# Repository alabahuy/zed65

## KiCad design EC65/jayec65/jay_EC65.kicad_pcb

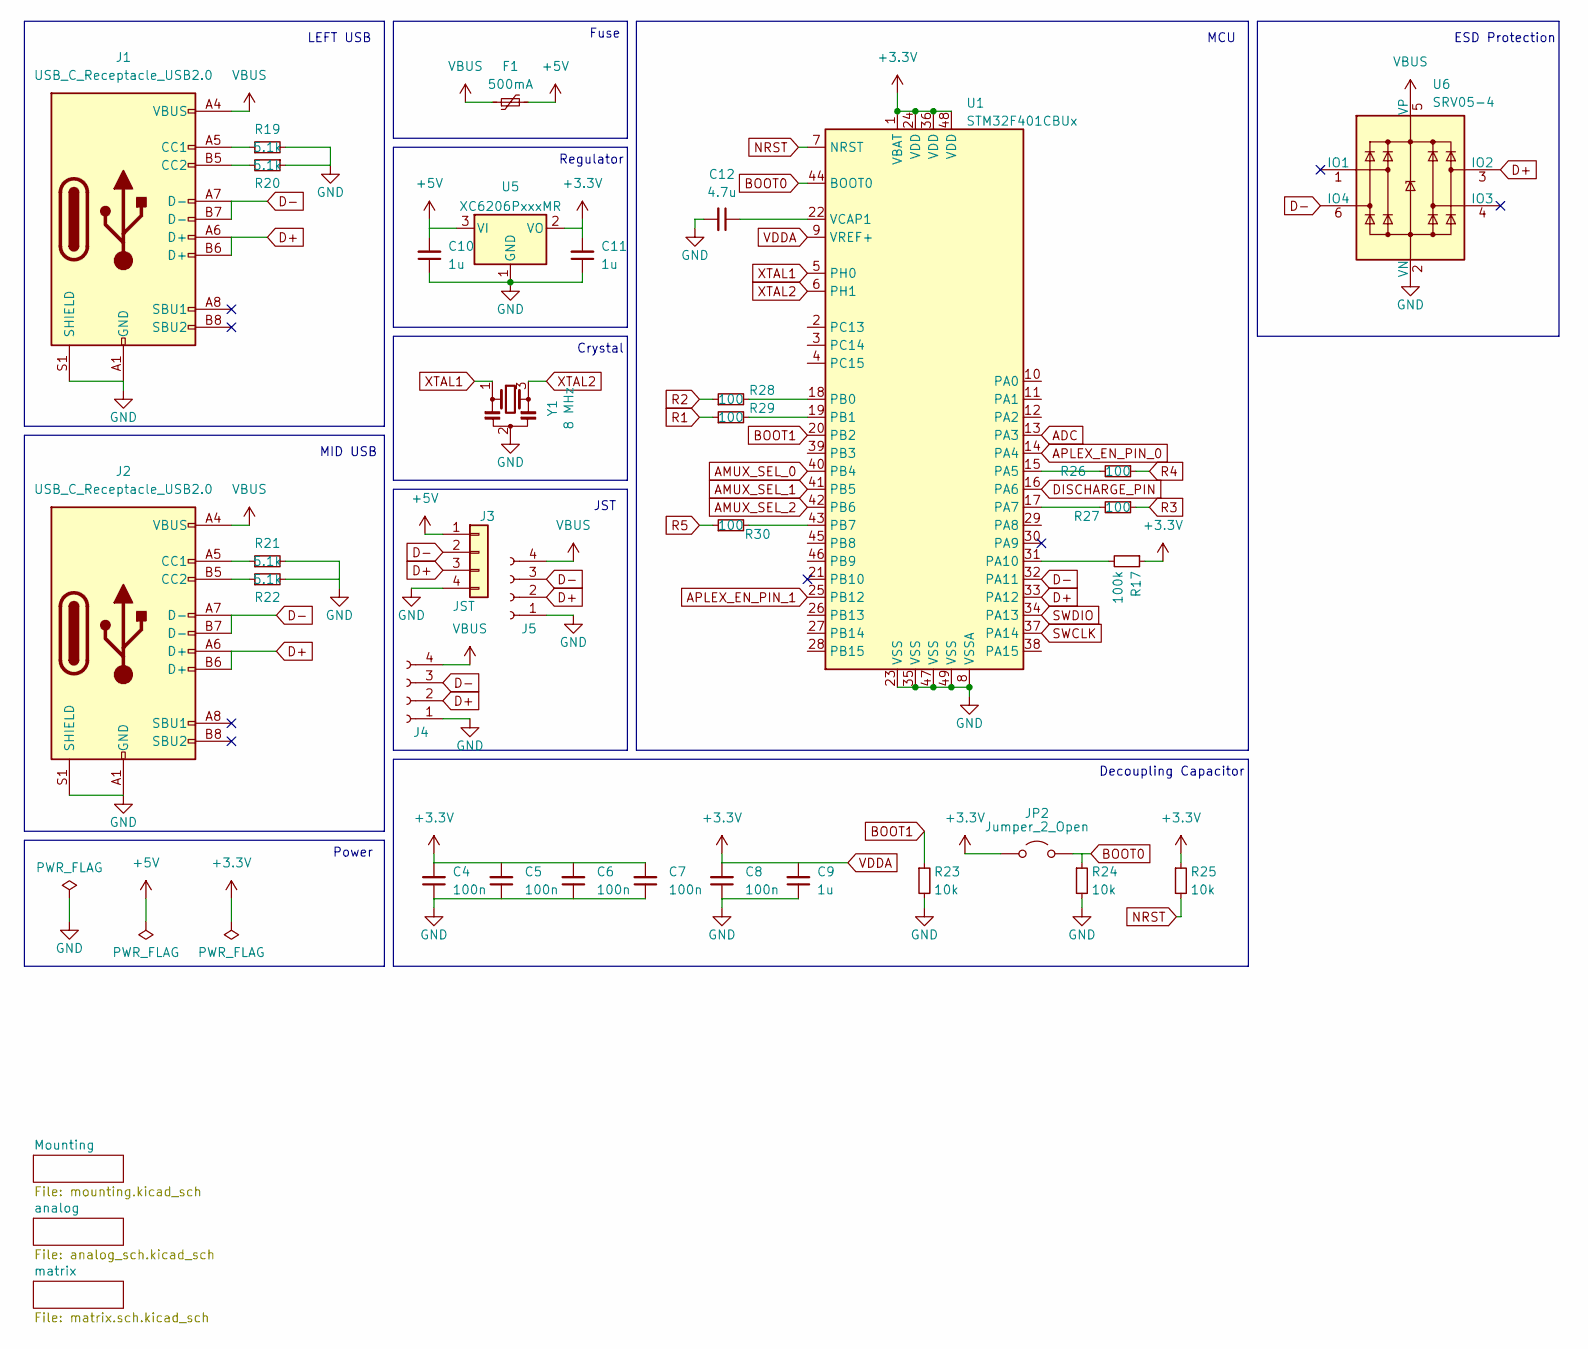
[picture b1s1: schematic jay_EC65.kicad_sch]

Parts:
C4, C5, C6, C7, C8: 100n; C_0603_1608Metric; LCSC C14663
C9, C10, C11: 1u; C_0603_1608Metric; LCSC C15849
C12: 4.7u; C_0603_1608Metric; LCSC C19666
F1: 500mA; Fuse_1206_3216Metric
J1, J2: USB_C_Receptacle_USB2.0; USB_C_Receptacle_HRO_TYPE-C-31-M-12
J3: JST; JST-SR-4; LCSC C145956
J4, J5: Conn_01x04_Socket; PinHeader_1x04_P2.00mm_Vertical
JP2: Jumper_2_Open; PinHeader_1x02_P2.54mm_Vertical
R17: 100k; R_0603_1608Metric; LCSC C25803
R19, R20, R21, R22: 5.1k; R_0603_1608Metric; LCSC C23186
R23, R24, R25: 10k; R_0603_1608Metric; LCSC C25804
R26, R27, R28, R29, R30: 100; R_0603_1608Metric; LCSC C22775
U1: STM32F401CBUx; QFN-48-1EP_7x7mm_P0.5mm_EP5.6x5.6mm; MPN C118825; LCSC C118825
U5: XC6206PxxxMR; SOT-23; LCSC C5446
U6: SRV05-4; SOT-23-6_Handsoldering; LCSC C7420376
Y1: 8 MHz; Resonator_SMD_Murata_CSTxExxV-3Pin_3.0x1.1mm; LCSC C907975

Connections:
+5V: C10.2, F1.2, J3.1
ADC: U1.13 (PA3); also elsewhere on the board
AMUX_SEL_0: U1.40 (PB4); also elsewhere on the board
AMUX_SEL_1: U1.41 (PB5); also elsewhere on the board
AMUX_SEL_2: U1.42 (PB6); also elsewhere on the board
APLEX_EN_PIN_0: U1.14 (PA4); also elsewhere on the board
APLEX_EN_PIN_1: U1.25 (PB12); also elsewhere on the board
APLEX_OUT_PIN_0: U1.16 (PA6); also elsewhere on the board
BOOT0: JP2.2 (B), U1.44 (BOOT0)
BOOT1: R23.1, U1.20 (PB2)
D+: J1.A6 (D+), J1.B6 (D+), J2.A6 (D+), J2.B6 (D+), J3.3, J4.2, J5.2, U1.33 (PA12), U6.3 (IO2)
D-: J1.A7 (D-), J1.B7 (D-), J2.A7 (D-), J2.B7 (D-), J3.2, J4.3, J5.3, U1.32 (PA11), U6.6 (IO4)
GND: C4.1, C7.1, C8.1, C9.1, C10.1, C11.1, C12.2, J1.A1 (GND), J1.A12 (GND), J1.B1 (GND), J1.B12 (GND), J1.S1 (SHIELD), J2.A1 (GND), J2.A12 (GND), J2.B1 (GND), J2.B12 (GND), J2.S1 (SHIELD), J3.4, J4.1, J5.1, R19.2, R20.1, R21.2, R23.2, R24.2, U1.8 (VSSA), U1.23 (VSS), U1.35 (VSS), U1.47 (VSS), U1.49 (VSS), U5.1 (GND), U6.2 (VN), Y1.2; also elsewhere on the board
NRST: R25.2, U1.7 (NRST)
unnamed: J1.A5 (CC1), R19.1
unnamed: J1.B5 (CC2), R20.2
unnamed: J2.A5 (CC1), R21.1
unnamed: J2.B5 (CC2), R22.1
unnamed: R26.2, U1.15 (PA5)
unnamed: R27.2, U1.17 (PA7)
unnamed: R17.2, U1.31 (PA10)
unnamed: R28.2, U1.18 (PB0)
unnamed: R29.2, U1.19 (PB1)
unnamed: R30.2, U1.43 (PB7)
unnamed: C12.1, U1.22 (VCAP1)
R1: R29.1; also elsewhere on the board
R2: R28.1; also elsewhere on the board
R3: R27.1; also elsewhere on the board
R4: R26.1; also elsewhere on the board
R5: R30.1; also elsewhere on the board
SWCLK: U1.37 (PA14)
SWDIO: U1.34 (PA13)
VBUS: F1.1, J1.A4 (VBUS), J1.A9 (VBUS), J1.B4 (VBUS), J1.B9 (VBUS), J2.A4 (VBUS), J2.A9 (VBUS), J2.B4 (VBUS), J2.B9 (VBUS), J4.4, J5.4, U6.5 (VP)
VDDA: C4.2, C7.2, C8.2, C11.2, JP2.1 (A), R17.1, R25.1, U1.1 (VBAT), U1.9 (VREF+), U1.24 (VDD), U1.36 (VDD), U1.48 (VDD); also elsewhere on the board
XTAL1: U1.5 (PH0), Y1.1
XTAL2: U1.6 (PH1), Y1.3

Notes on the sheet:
Crystal
LEFT USB
Decoupling Capacitor
JST
MID USB
MCU
ESD Protection
Power
Fuse
Regulator

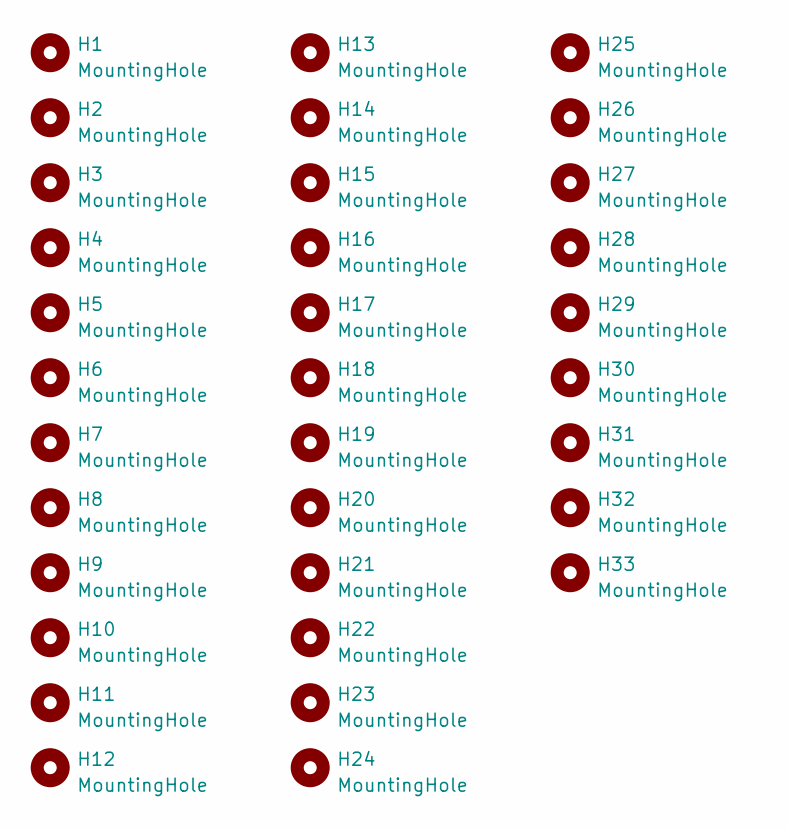
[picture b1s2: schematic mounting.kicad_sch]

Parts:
H1, H2, H3, H4, H5, H6, H7, H8, H9, H10, H11, H12, H13, H14, H15, H16, H17, H18, H19, H20, H21, H22, H23, H24, H25, H26, H27, H28, H29, H30, H31, H32, H33: MountingHole; HOLE_M2

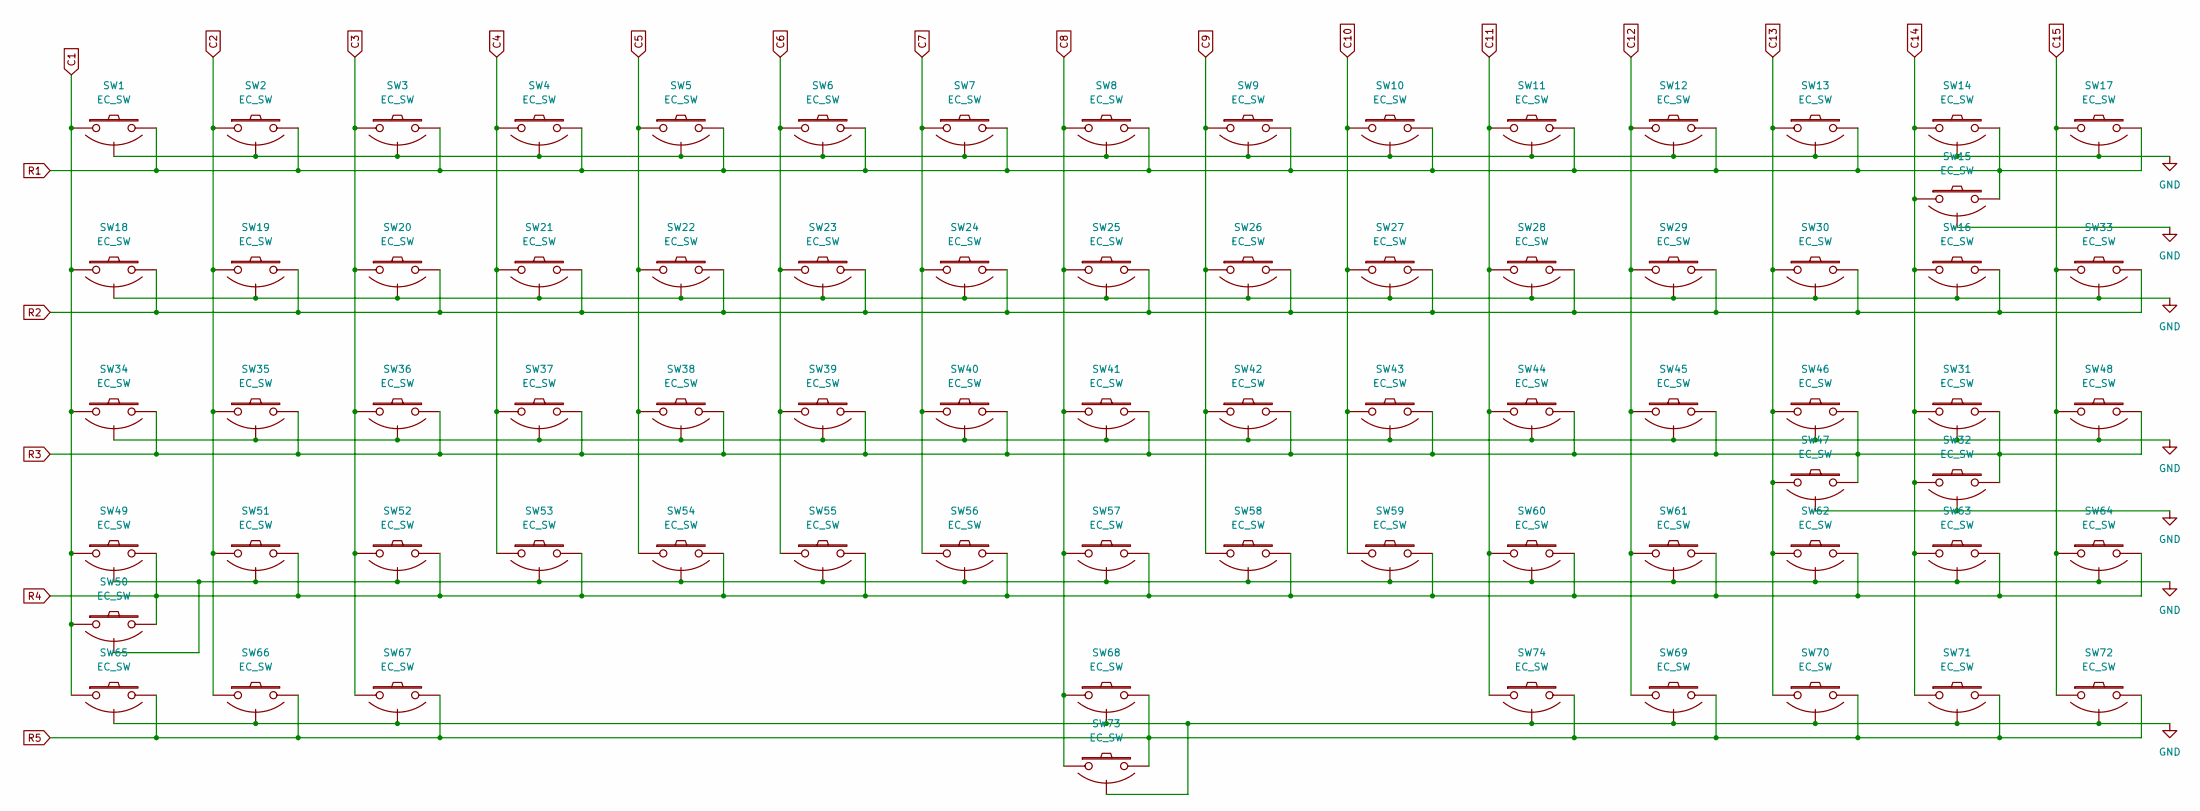
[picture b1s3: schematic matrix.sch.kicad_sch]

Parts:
SW1: EC_SW; ecs_pad_1U_no_ring_ 東プレ _十六条旭日旗
SW2, SW3, SW4, SW5, SW6, SW7, SW8, SW9, SW10, SW11, SW12, SW13, SW14, SW16, SW17, SW18, SW19, SW20, SW21, SW22, SW23, SW24, SW25, SW26, SW27, SW28, SW29, SW30, SW31, SW33, SW35, SW36, SW37, SW38, SW39, SW40, SW41, SW42, SW43, SW44, SW45, SW46, SW48, SW49, SW51, SW52, SW53, SW54, SW55, SW56, SW57, SW58, SW59, SW60, SW61, SW62, SW63, SW64, SW68, SW70, SW71, SW72, SW73, SW74: EC_SW; ecs_pad_1U_no_ring
SW15, SW32, SW47, SW50: EC_SW; ecs_pad_2U_no_ring
SW34: EC_SW; ecs_pad_0.25U_spaced_no_ring
SW65, SW66, SW67, SW69: EC_SW; ecs_pad_0.125U_spaced_no_ring

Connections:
C1: SW1.1, SW18.1, SW34.1, SW49.1, SW50.1, SW65.1; also elsewhere on the board
C2: SW2.1, SW19.1, SW35.1, SW51.1, SW66.1; also elsewhere on the board
C3: SW3.1, SW20.1, SW36.1, SW52.1, SW67.1; also elsewhere on the board
C4: SW4.1, SW21.1, SW37.1, SW53.1; also elsewhere on the board
C5: SW5.1, SW22.1, SW38.1, SW54.1; also elsewhere on the board
C6: SW6.1, SW23.1, SW39.1, SW55.1; also elsewhere on the board
C7: SW7.1, SW24.1, SW40.1, SW56.1; also elsewhere on the board
C8: SW8.1, SW25.1, SW41.1, SW57.1, SW68.1, SW73.1; also elsewhere on the board
C9: SW9.1, SW26.1, SW42.1, SW58.1; also elsewhere on the board
C10: SW10.1, SW27.1, SW43.1, SW59.1; also elsewhere on the board
C11: SW11.1, SW28.1, SW44.1, SW60.1, SW74.1; also elsewhere on the board
C12: SW12.1, SW29.1, SW45.1, SW61.1, SW69.1; also elsewhere on the board
C13: SW13.1, SW30.1, SW46.1, SW47.1, SW62.1, SW70.1; also elsewhere on the board
C14: SW14.1, SW15.1, SW16.1, SW31.1, SW32.1, SW63.1, SW71.1; also elsewhere on the board
C15: SW17.1, SW33.1, SW48.1, SW64.1, SW72.1; also elsewhere on the board
GND: SW1.3 (SG), SW2.3 (SG), SW3.3 (SG), SW4.3 (SG), SW5.3 (SG), SW6.3 (SG), SW7.3 (SG), SW8.3 (SG), SW9.3 (SG), SW10.3 (SG), SW11.3 (SG), SW12.3 (SG), SW13.3 (SG), SW14.3 (SG), SW15.3 (SG), SW16.3 (SG), SW17.3 (SG), SW18.3 (SG), SW19.3 (SG), SW20.3 (SG), SW21.3 (SG), SW22.3 (SG), SW23.3 (SG), SW24.3 (SG), SW25.3 (SG), SW26.3 (SG), SW27.3 (SG), SW28.3 (SG), SW29.3 (SG), SW30.3 (SG), SW31.3 (SG), SW32.3 (SG), SW33.3 (SG), SW34.3 (SG), SW35.3 (SG), SW36.3 (SG), SW37.3 (SG), SW38.3 (SG), SW39.3 (SG), SW40.3 (SG), SW41.3 (SG), SW42.3 (SG), SW43.3 (SG), SW44.3 (SG), SW45.3 (SG), SW46.3 (SG), SW47.3 (SG), SW48.3 (SG), SW49.3 (SG), SW50.3 (SG), SW51.3 (SG), SW52.3 (SG), SW53.3 (SG), SW54.3 (SG), SW55.3 (SG), SW56.3 (SG), SW57.3 (SG), SW58.3 (SG), SW59.3 (SG), SW60.3 (SG), SW61.3 (SG), SW62.3 (SG), SW63.3 (SG), SW64.3 (SG), SW65.3 (SG), SW66.3 (SG), SW67.3 (SG), SW68.3 (SG), SW69.3 (SG), SW70.3 (SG), SW71.3 (SG), SW72.3 (SG), SW73.3 (SG), SW74.3 (SG); also elsewhere on the board
R1: SW1.2, SW2.2, SW3.2, SW4.2, SW5.2, SW6.2, SW7.2, SW8.2, SW9.2, SW10.2, SW11.2, SW12.2, SW13.2, SW14.2, SW15.2, SW17.2; also elsewhere on the board
R2: SW16.2, SW18.2, SW19.2, SW20.2, SW21.2, SW22.2, SW23.2, SW24.2, SW25.2, SW26.2, SW27.2, SW28.2, SW29.2, SW30.2, SW33.2; also elsewhere on the board
R3: SW31.2, SW32.2, SW34.2, SW35.2, SW36.2, SW37.2, SW38.2, SW39.2, SW40.2, SW41.2, SW42.2, SW43.2, SW44.2, SW45.2, SW46.2, SW47.2, SW48.2; also elsewhere on the board
R4: SW49.2, SW50.2, SW51.2, SW52.2, SW53.2, SW54.2, SW55.2, SW56.2, SW57.2, SW58.2, SW59.2, SW60.2, SW61.2, SW62.2, SW63.2, SW64.2; also elsewhere on the board
R5: SW65.2, SW66.2, SW67.2, SW68.2, SW69.2, SW70.2, SW71.2, SW72.2, SW73.2, SW74.2; also elsewhere on the board

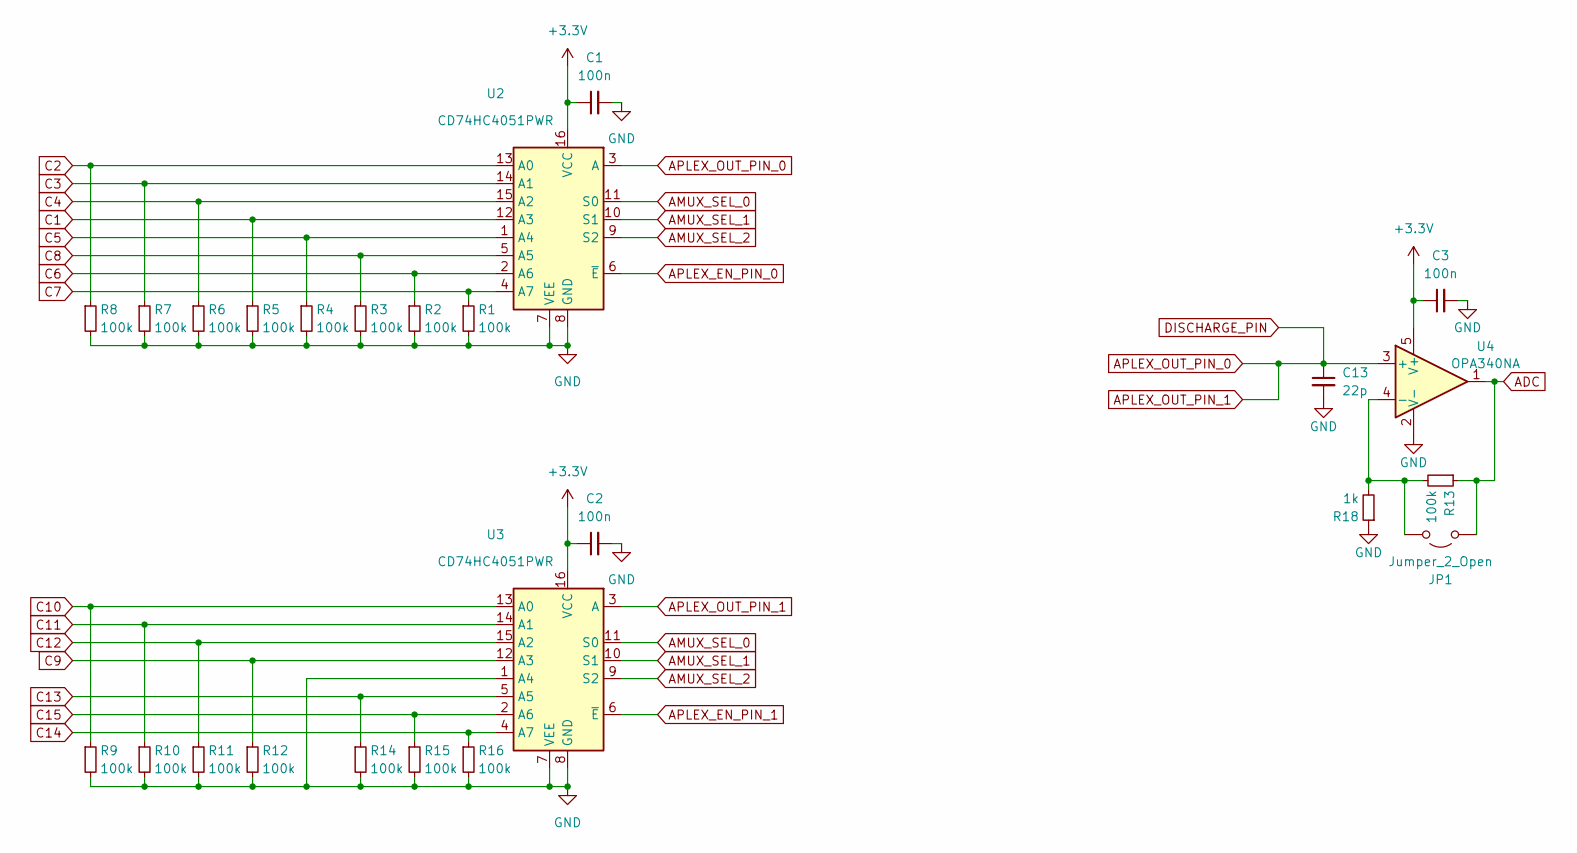
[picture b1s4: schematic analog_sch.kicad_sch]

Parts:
C1, C2, C3: 100n; C_0603_1608Metric; LCSC C14663
C13: 22p; C_0603_1608Metric; LCSC C183114
JP1: Jumper_2_Open; R_0603_1608Metric_Pad0.98x0.95mm_HandSolder
R1, R2, R3, R4, R5, R6, R7, R8, R9, R10, R11, R12, R13, R14, R15, R16: 100k; R_0603_1608Metric; LCSC C25803
R18: 1k; R_0603_1608Metric; LCSC C21190
U2, U3: CD74HC4051PWR; TSSOP16; MPN CD74HC4051PWR; LCSC C352826
U4: OPA340NA; SOT-23-5; MPN OPA340NA/3K; LCSC C73479

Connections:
ADC: JP1.1 (A), R13.1, U4.1; also elsewhere on the board
AMUX_SEL_0: U2.11 (S0), U3.11 (S0); also elsewhere on the board
AMUX_SEL_1: U2.10 (S1), U3.10 (S1); also elsewhere on the board
AMUX_SEL_2: U2.9 (S2), U3.9 (S2); also elsewhere on the board
APLEX_EN_PIN_0: U2.6 (~E); also elsewhere on the board
APLEX_EN_PIN_1: U3.6 (~E); also elsewhere on the board
APLEX_OUT_PIN_0: C13.1, U2.3 (A), U3.3 (A), U4.3 (+); also elsewhere on the board
C1: R5.1, U2.12 (A3); also elsewhere on the board
C2: R8.1, U2.13 (A0); also elsewhere on the board
C3: R7.1, U2.14 (A1); also elsewhere on the board
C4: R6.1, U2.15 (A2); also elsewhere on the board
C5: R4.1, U2.1 (A4); also elsewhere on the board
C6: R2.1, U2.2 (A6); also elsewhere on the board
C7: R1.1, U2.4 (A7); also elsewhere on the board
C8: R3.1, U2.5 (A5); also elsewhere on the board
C9: R12.1, U3.12 (A3); also elsewhere on the board
C10: R9.1, U3.13 (A0); also elsewhere on the board
C11: R10.1, U3.14 (A1); also elsewhere on the board
C12: R11.1, U3.15 (A2); also elsewhere on the board
C13: R14.1, U3.5 (A5); also elsewhere on the board
C14: R16.1, U3.4 (A7); also elsewhere on the board
C15: R15.1, U3.2 (A6); also elsewhere on the board
GND: C1.2, C2.2, C3.2, C13.2, R1.2, R2.2, R3.2, R4.2, R5.2, R6.2, R7.2, R8.2, R9.2, R10.2, R11.2, R12.2, R14.2, R15.2, R16.2, R18.1, U2.7 (VEE), U2.8 (GND), U3.1 (A4), U3.7 (VEE), U3.8 (GND), U4.2 (V-); also elsewhere on the board
unnamed: JP1.2 (B), R13.2, R18.2, U4.4 (-)
VDDA: C1.1, C2.1, C3.1, U2.16 (VCC), U3.16 (VCC), U4.5 (V+); also elsewhere on the board

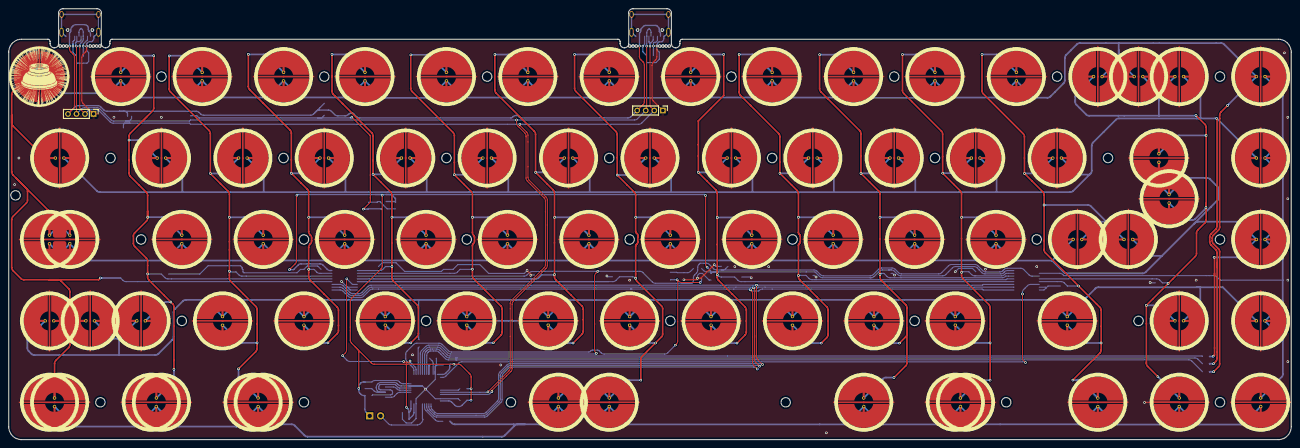
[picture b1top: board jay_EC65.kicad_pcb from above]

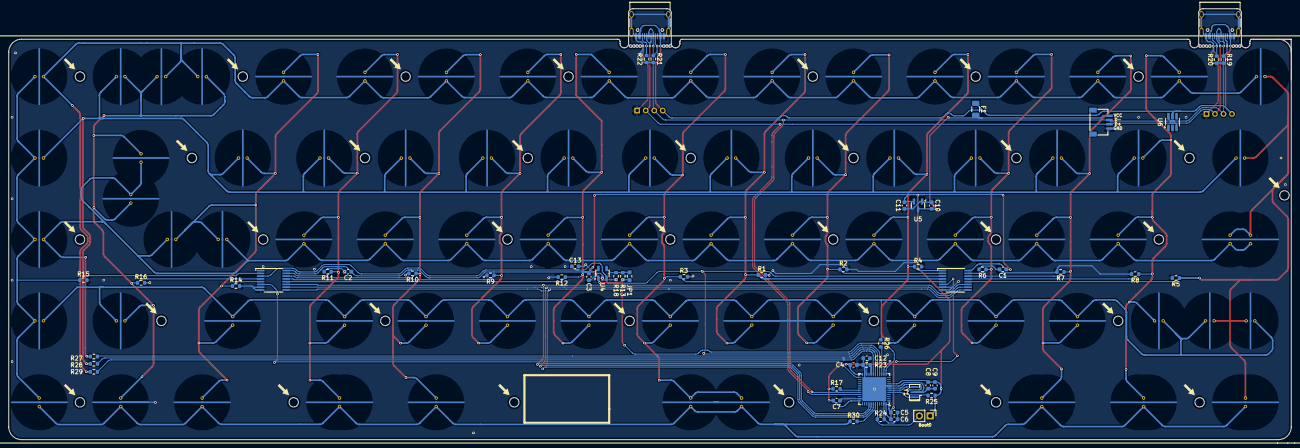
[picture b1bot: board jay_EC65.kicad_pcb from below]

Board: 2 copper layers, 300.0 x 100.8 mm, 165 parts (56 on the bottom side), 50 nets.

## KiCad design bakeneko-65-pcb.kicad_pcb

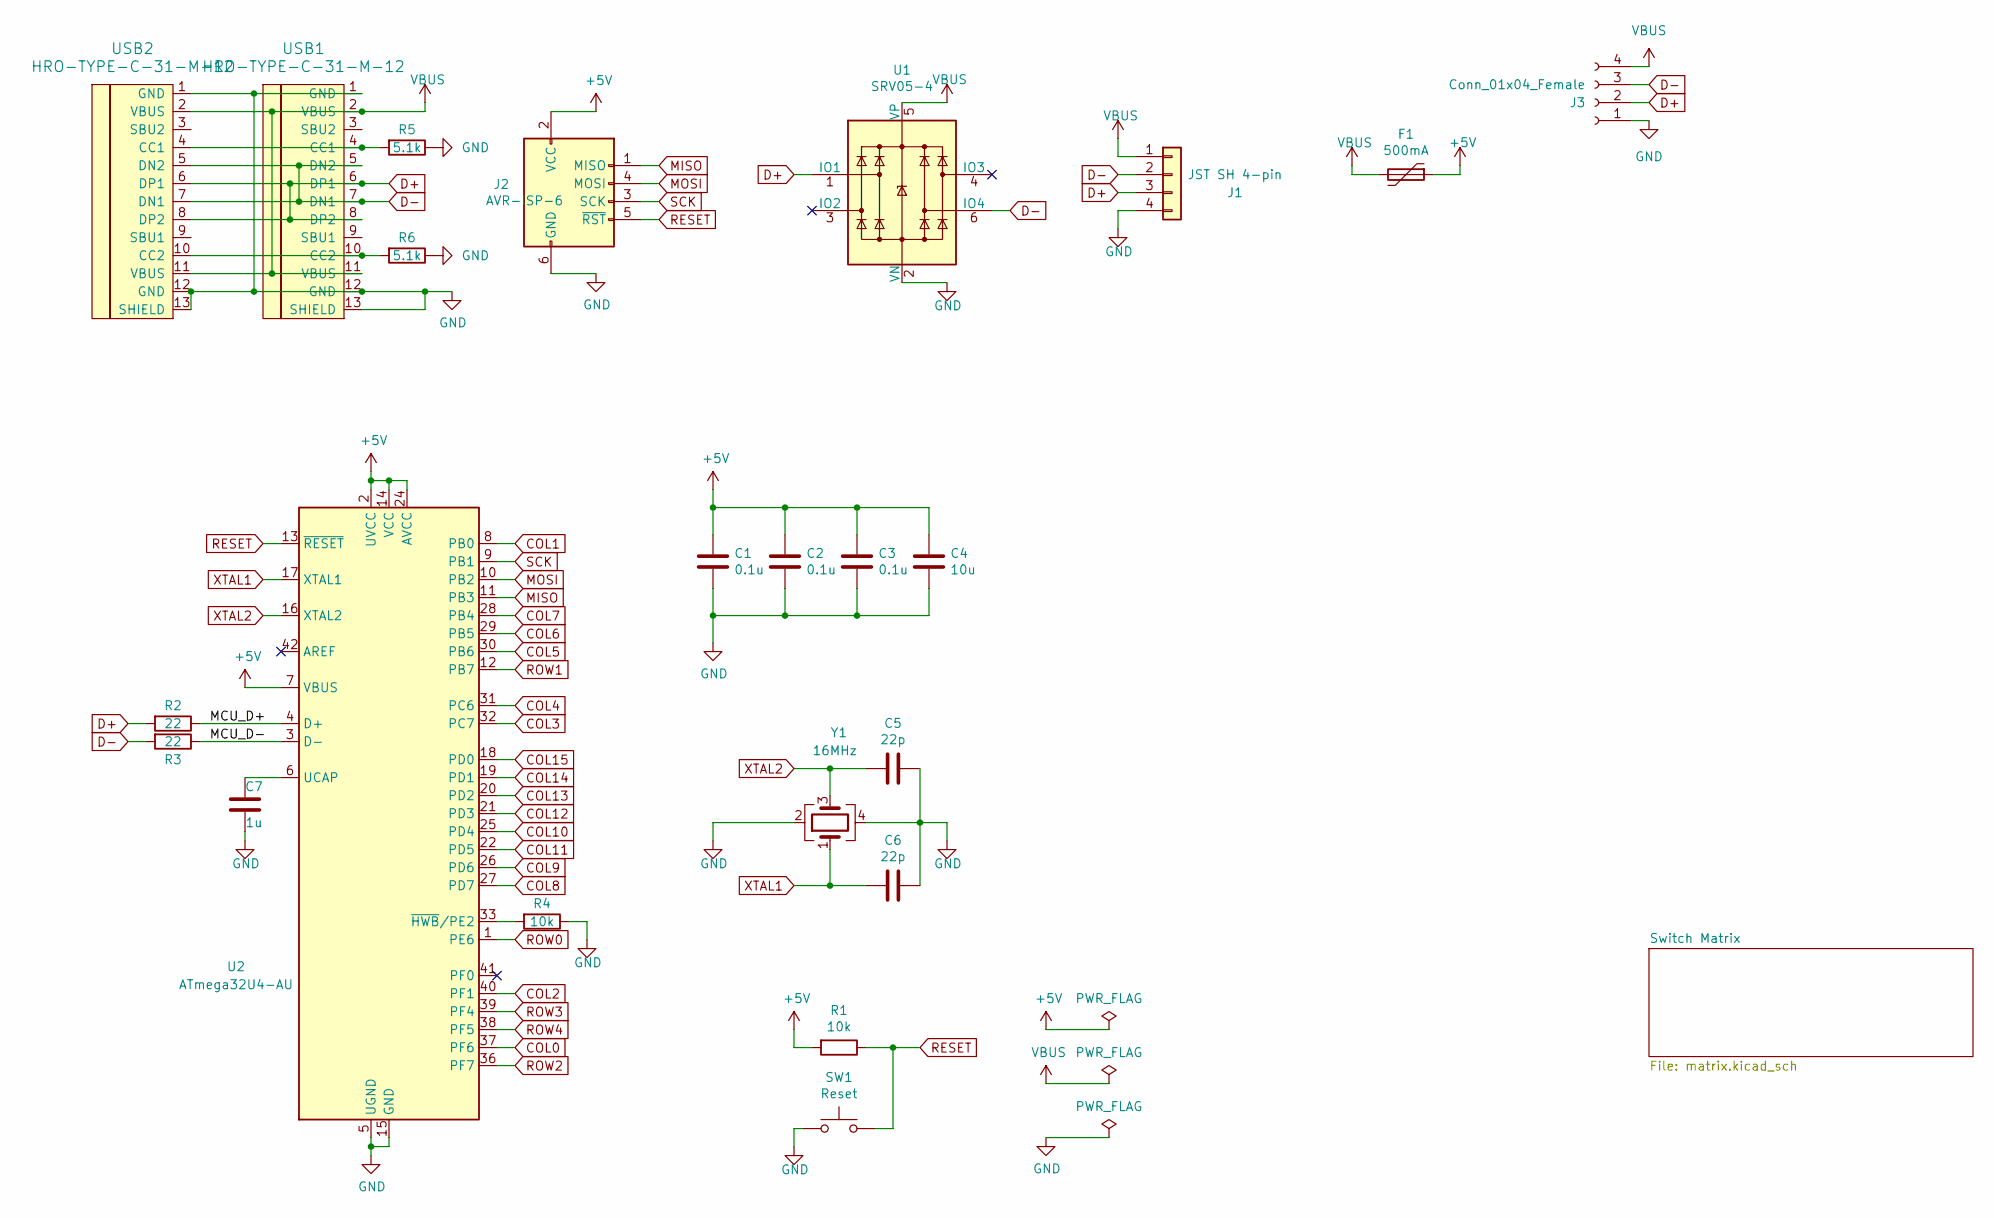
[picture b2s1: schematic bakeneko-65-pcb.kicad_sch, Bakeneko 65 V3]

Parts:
C1, C2, C3: 0.1u; C_0805_2012Metric; LCSC Part # C49678
C4: 10u; C_0805_2012Metric; LCSC Part # C15850
C5, C6: 22p; C_0805_2012Metric; LCSC Part # C1804
C7: 1u; C_0805_2012Metric; LCSC Part # C28323
F1: 500mA; Fuse_1206_3216Metric; LCSC Part # C70076
J1: JST SH 4-pin; JST_SH_SM04B-SRSS-TB_1x04-1MP_P1.00mm_Horizontal; LCSC Part # C160404
J2: AVR-ISP-6; ISP
J3: Conn_01x04_Female; PinHeader_1x04_P1.00mm_Vertical
R1, R4: 10k; R_0805_2012Metric; LCSC Part # C17414
R2, R3: 22; R_0805_2012Metric; LCSC Part # C17561
R5, R6: 5.1k; R_0805_2012Metric; LCSC Part # C17414
SW1: Reset; SW_SPST_TL3342; LCSC Part # C318884
U1: SRV05-4; SOT-23-6; LCSC Part # C85364
U2: ATmega32U4-AU; Hybrid Atmega32u4; LCSC Part # C44854
USB1, USB2: HRO-TYPE-C-31-M-12
Y1: 16MHz; Crystal_SMD_3225-4Pin_3.2x2.5mm; LCSC Part # C13738

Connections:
+5V: C1.1, C2.1, C3.1, C4.1, F1.1, J2.2 (VCC), R1.2, U2.2 (UVCC), U2.7 (VBUS), U2.14 (VCC), U2.24 (AVCC), U2.34 (VCC), U2.44 (AVCC)
/MCU_D+: R2.1, U2.4 (D+)
/MCU_D-: R3.1, U2.3 (D-)
COL0: U2.37 (PF6); also elsewhere on the board
COL1: U2.8 (PB0); also elsewhere on the board
COL2: U2.40 (PF1); also elsewhere on the board
COL3: U2.32 (PC7); also elsewhere on the board
COL4: U2.31 (PC6); also elsewhere on the board
COL5: U2.30 (PB6); also elsewhere on the board
COL6: U2.29 (PB5); also elsewhere on the board
COL7: U2.28 (PB4); also elsewhere on the board
COL8: U2.27 (PD7); also elsewhere on the board
COL9: U2.26 (PD6); also elsewhere on the board
COL10: U2.25 (PD4); also elsewhere on the board
COL11: U2.22 (PD5); also elsewhere on the board
COL12: U2.21 (PD3); also elsewhere on the board
COL13: U2.20 (PD2); also elsewhere on the board
COL14: U2.19 (PD1); also elsewhere on the board
COL15: U2.18 (PD0); also elsewhere on the board
D+: J1.3, J3.2, R2.2, U1.1 (IO1), USB1.6 (DP1), USB1.8 (DP2), USB2.6 (DP1), USB2.8 (DP2)
D-: J1.2, J3.3, R3.2, U1.6 (IO4), USB1.5 (DN2), USB1.7 (DN1), USB2.5 (DN2), USB2.7 (DN1)
GND: C1.2, C2.2, C3.2, C4.2, C5.1, C6.1, C7.2, J1.4, J2.6 (GND), J3.1, R4.1, R5.1, R6.1, SW1.1, U1.2 (VN), U2.5 (UGND), U2.15 (GND), U2.23 (GND), U2.35 (GND), U2.43 (GND), USB1.1 (GND), USB1.12 (GND), USB1.13 (SHIELD), USB2.1 (GND), USB2.12 (GND), USB2.13 (SHIELD), Y1.2, Y1.4
MISO: J2.1 (MISO), U2.11 (PB3)
MOSI: J2.4 (MOSI), U2.10 (PB2)
unnamed: C7.1, U2.6 (UCAP)
unnamed: R4.2, U2.33 (~HWB/PE2)
unnamed: R5.2, USB1.4 (CC1), USB2.4 (CC1)
unnamed: R6.2, USB1.10 (CC2), USB2.10 (CC2)
RESET: J2.5 (~RST), R1.1, SW1.2, U2.13 (~RESET)
ROW0: U2.1 (PE6); also elsewhere on the board
ROW1: U2.12 (PB7); also elsewhere on the board
ROW2: U2.36 (PF7); also elsewhere on the board
ROW3: U2.39 (PF4); also elsewhere on the board
ROW4: U2.38 (PF5); also elsewhere on the board
SCK: J2.3 (SCK), U2.9 (PB1)
VBUS: F1.2, J1.1, J3.4, U1.5 (VP), USB1.2 (VBUS), USB1.11 (VBUS), USB2.2 (VBUS), USB2.11 (VBUS)
XTAL1: C6.2, U2.17 (XTAL1), Y1.1
XTAL2: C5.2, U2.16 (XTAL2), Y1.3

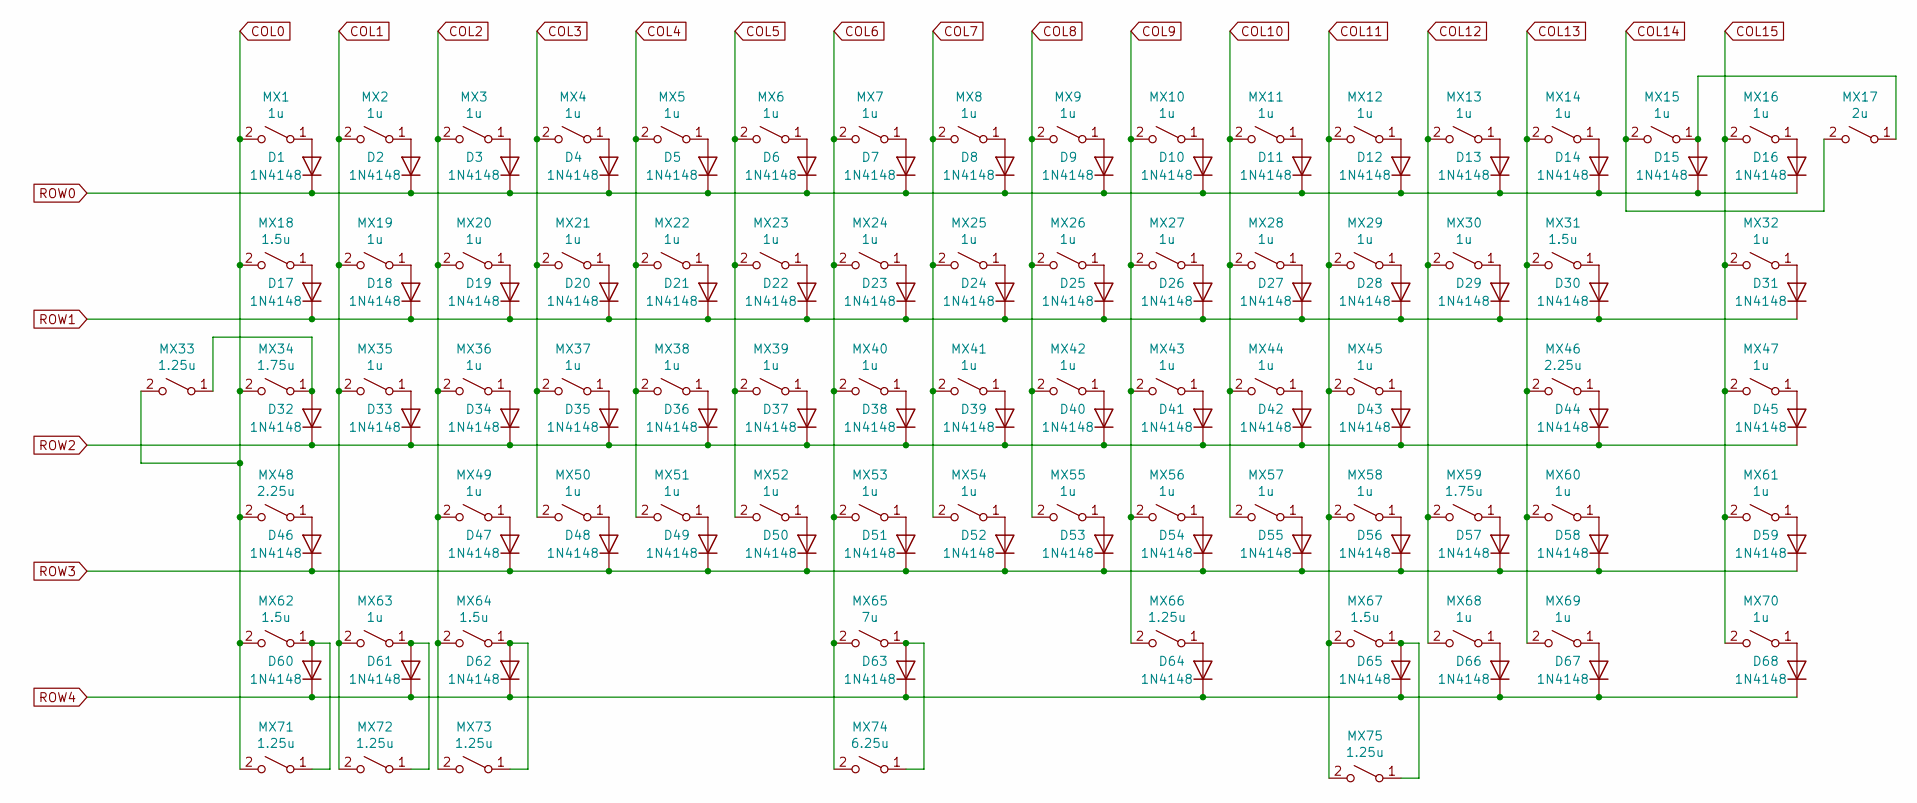
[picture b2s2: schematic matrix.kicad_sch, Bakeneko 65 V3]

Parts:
D1, D2, D3, D4, D5, D6, D7, D8, D9, D10, D11, D12, D13, D14, D15, D16, D17, D18, D19, D20, D21, D22, D23, D24, D25, D26, D27, D28, D29, D30, D31, D32, D33, D34, D35, D36, D37, D38, D39, D40, D41, D42, D43, D44, D45, D46, D47, D48, D49, D50, D51, D52, D53, D54, D55, D56, D57, D58, D59, D60, D61, D62, D63, D64, D65, D66, D67, D68: 1N4148; D_SOD-123; LCSC Part # C81598
MX1, MX2, MX3, MX4, MX5, MX6, MX7, MX8, MX9, MX10, MX11, MX12, MX13, MX14, MX15, MX16, MX19, MX20, MX21, MX22, MX23, MX24, MX25, MX26, MX27, MX28, MX29, MX30, MX32, MX35, MX36, MX37, MX38, MX39, MX40, MX41, MX42, MX43, MX44, MX45, MX47, MX49, MX50, MX51, MX52, MX53, MX54, MX55, MX56, MX57, MX58, MX60, MX61, MX63, MX68, MX69, MX70: 1u; MXOnly-1U-NoLED
MX17: 2u; MXOnly-2U-NoLED
MX18, MX31, MX62, MX64, MX67: 1.5u; MXOnly-1.5U-NoLED
MX33, MX66, MX71, MX72, MX73, MX75: 1.25u; MXOnly-1.25U-NoLED
MX34, MX59: 1.75u; MXOnly-1.75U-NoLED
MX46, MX48: 2.25u; MXOnly-2.25U-NoLED
MX65: 7u; MXOnly-7U-ReversedStabilizers-NoLED
MX74: 6.25u; MXOnly-6.25U-ReversedStabilizers-NoLED

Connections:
COL0: MX1.2 (B), MX18.2 (B), MX33.2 (B), MX34.2 (B), MX48.2 (B), MX62.2 (B), MX71.2 (B); also elsewhere on the board
COL1: MX2.2 (B), MX19.2 (B), MX35.2 (B), MX63.2 (B), MX72.2 (B); also elsewhere on the board
COL2: MX3.2 (B), MX20.2 (B), MX36.2 (B), MX49.2 (B), MX64.2 (B), MX73.2 (B); also elsewhere on the board
COL3: MX4.2 (B), MX21.2 (B), MX37.2 (B), MX50.2 (B); also elsewhere on the board
COL4: MX5.2 (B), MX22.2 (B), MX38.2 (B), MX51.2 (B); also elsewhere on the board
COL5: MX6.2 (B), MX23.2 (B), MX39.2 (B), MX52.2 (B); also elsewhere on the board
COL6: MX7.2 (B), MX24.2 (B), MX40.2 (B), MX53.2 (B), MX65.2 (B), MX74.2 (B); also elsewhere on the board
COL7: MX8.2 (B), MX25.2 (B), MX41.2 (B), MX54.2 (B); also elsewhere on the board
COL8: MX9.2 (B), MX26.2 (B), MX42.2 (B), MX55.2 (B); also elsewhere on the board
COL9: MX10.2 (B), MX27.2 (B), MX43.2 (B), MX56.2 (B), MX66.2 (B); also elsewhere on the board
COL10: MX11.2 (B), MX28.2 (B), MX44.2 (B), MX57.2 (B); also elsewhere on the board
COL11: MX12.2 (B), MX29.2 (B), MX45.2 (B), MX58.2 (B), MX67.2 (B), MX75.2 (B); also elsewhere on the board
COL12: MX13.2 (B), MX30.2 (B), MX59.2 (B), MX68.2 (B); also elsewhere on the board
COL13: MX14.2 (B), MX31.2 (B), MX46.2 (B), MX60.2 (B), MX69.2 (B); also elsewhere on the board
COL14: MX15.2 (B), MX17.2 (B); also elsewhere on the board
COL15: MX16.2 (B), MX32.2 (B), MX47.2 (B), MX61.2 (B), MX70.2 (B); also elsewhere on the board
unnamed: D1.2 (A), MX1.1 (A)
unnamed: D2.2 (A), MX2.1 (A)
unnamed: D3.2 (A), MX3.1 (A)
unnamed: D4.2 (A), MX4.1 (A)
unnamed: D5.2 (A), MX5.1 (A)
unnamed: D6.2 (A), MX6.1 (A)
unnamed: D7.2 (A), MX7.1 (A)
unnamed: D8.2 (A), MX8.1 (A)
unnamed: D9.2 (A), MX9.1 (A)
unnamed: D10.2 (A), MX10.1 (A)
unnamed: D11.2 (A), MX11.1 (A)
unnamed: D12.2 (A), MX12.1 (A)
unnamed: D13.2 (A), MX13.1 (A)
unnamed: D14.2 (A), MX14.1 (A)
unnamed: D15.2 (A), MX15.1 (A), MX17.1 (A)
unnamed: D16.2 (A), MX16.1 (A)
unnamed: D17.2 (A), MX18.1 (A)
unnamed: D18.2 (A), MX19.1 (A)
unnamed: D19.2 (A), MX20.1 (A)
unnamed: D20.2 (A), MX21.1 (A)
unnamed: D21.2 (A), MX22.1 (A)
unnamed: D22.2 (A), MX23.1 (A)
unnamed: D23.2 (A), MX24.1 (A)
unnamed: D24.2 (A), MX25.1 (A)
unnamed: D25.2 (A), MX26.1 (A)
unnamed: D26.2 (A), MX27.1 (A)
unnamed: D27.2 (A), MX28.1 (A)
unnamed: D28.2 (A), MX29.1 (A)
unnamed: D29.2 (A), MX30.1 (A)
unnamed: D30.2 (A), MX31.1 (A)
unnamed: D31.2 (A), MX32.1 (A)
unnamed: D32.2 (A), MX33.1 (A), MX34.1 (A)
unnamed: D33.2 (A), MX35.1 (A)
unnamed: D34.2 (A), MX36.1 (A)
unnamed: D35.2 (A), MX37.1 (A)
unnamed: D36.2 (A), MX38.1 (A)
unnamed: D37.2 (A), MX39.1 (A)
unnamed: D38.2 (A), MX40.1 (A)
unnamed: D39.2 (A), MX41.1 (A)
unnamed: D40.2 (A), MX42.1 (A)
unnamed: D41.2 (A), MX43.1 (A)
unnamed: D42.2 (A), MX44.1 (A)
unnamed: D43.2 (A), MX45.1 (A)
unnamed: D44.2 (A), MX46.1 (A)
unnamed: D45.2 (A), MX47.1 (A)
unnamed: D46.2 (A), MX48.1 (A)
unnamed: D47.2 (A), MX49.1 (A)
unnamed: D48.2 (A), MX50.1 (A)
unnamed: D49.2 (A), MX51.1 (A)
unnamed: D50.2 (A), MX52.1 (A)
unnamed: D51.2 (A), MX53.1 (A)
unnamed: D52.2 (A), MX54.1 (A)
unnamed: D53.2 (A), MX55.1 (A)
unnamed: D54.2 (A), MX56.1 (A)
unnamed: D55.2 (A), MX57.1 (A)
unnamed: D56.2 (A), MX58.1 (A)
unnamed: D57.2 (A), MX59.1 (A)
unnamed: D58.2 (A), MX60.1 (A)
unnamed: D59.2 (A), MX61.1 (A)
unnamed: D60.2 (A), MX62.1 (A), MX71.1 (A)
unnamed: D61.2 (A), MX63.1 (A), MX72.1 (A)
unnamed: D62.2 (A), MX64.1 (A), MX73.1 (A)
unnamed: D63.2 (A), MX65.1 (A), MX74.1 (A)
unnamed: D64.2 (A), MX66.1 (A)
unnamed: D65.2 (A), MX67.1 (A), MX75.1 (A)
unnamed: D66.2 (A), MX68.1 (A)
unnamed: D67.2 (A), MX69.1 (A)
unnamed: D68.2 (A), MX70.1 (A)
ROW0: D1.1 (K), D2.1 (K), D3.1 (K), D4.1 (K), D5.1 (K), D6.1 (K), D7.1 (K), D8.1 (K), D9.1 (K), D10.1 (K), D11.1 (K), D12.1 (K), D13.1 (K), D14.1 (K), D15.1 (K), D16.1 (K); also elsewhere on the board
ROW1: D17.1 (K), D18.1 (K), D19.1 (K), D20.1 (K), D21.1 (K), D22.1 (K), D23.1 (K), D24.1 (K), D25.1 (K), D26.1 (K), D27.1 (K), D28.1 (K), D29.1 (K), D30.1 (K), D31.1 (K); also elsewhere on the board
ROW2: D32.1 (K), D33.1 (K), D34.1 (K), D35.1 (K), D36.1 (K), D37.1 (K), D38.1 (K), D39.1 (K), D40.1 (K), D41.1 (K), D42.1 (K), D43.1 (K), D44.1 (K), D45.1 (K); also elsewhere on the board
ROW3: D46.1 (K), D47.1 (K), D48.1 (K), D49.1 (K), D50.1 (K), D51.1 (K), D52.1 (K), D53.1 (K), D54.1 (K), D55.1 (K), D56.1 (K), D57.1 (K), D58.1 (K), D59.1 (K); also elsewhere on the board
ROW4: D60.1 (K), D61.1 (K), D62.1 (K), D63.1 (K), D64.1 (K), D65.1 (K), D66.1 (K), D67.1 (K), D68.1 (K); also elsewhere on the board

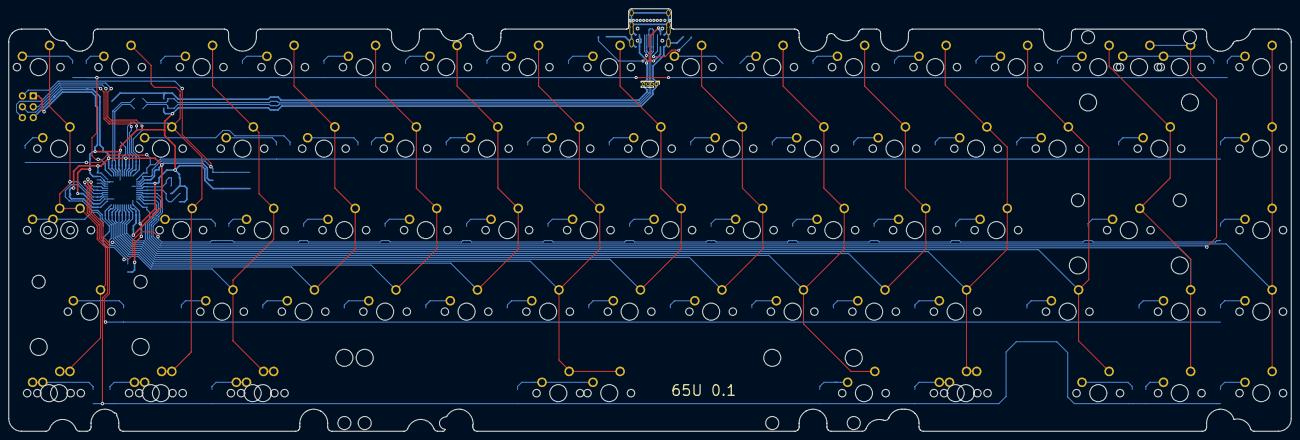
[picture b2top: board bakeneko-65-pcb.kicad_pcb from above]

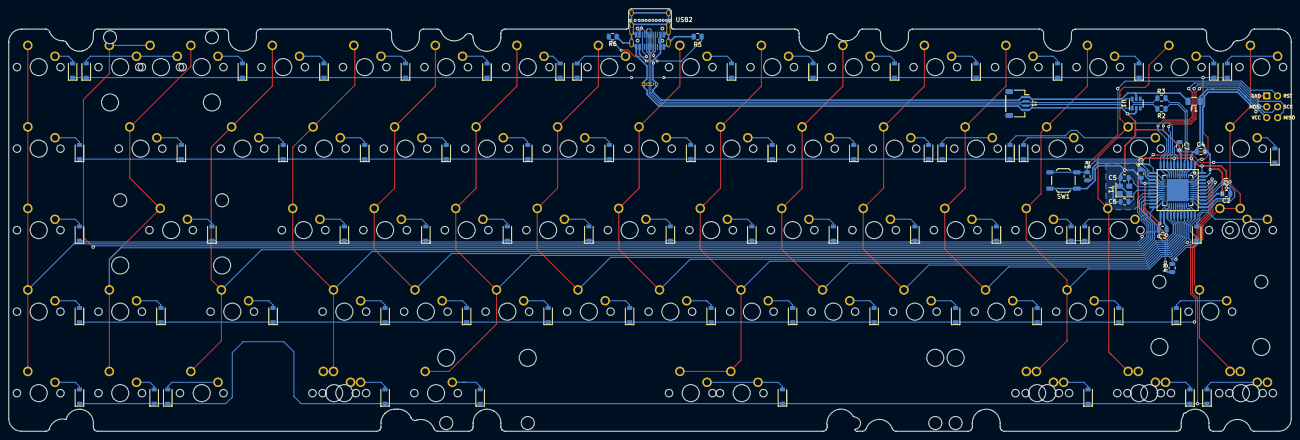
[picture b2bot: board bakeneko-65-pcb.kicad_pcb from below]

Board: 2 copper layers, 299.8 x 98.7 mm, 166 parts (90 on the bottom side), 106 nets.

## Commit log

2023-10-02 remove
2023-10-03 remove usb
2023-10-04 add USB c
2023-10-05 change Atmega AU to MU
2024-07-27 add jayec

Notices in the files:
bakeneko-65-pcb.kicad_sch:
Copyright © 2020 kkatano
MIT License
